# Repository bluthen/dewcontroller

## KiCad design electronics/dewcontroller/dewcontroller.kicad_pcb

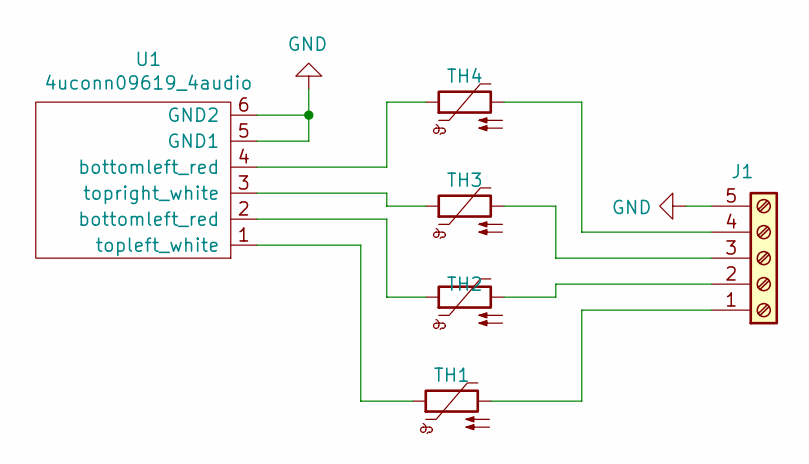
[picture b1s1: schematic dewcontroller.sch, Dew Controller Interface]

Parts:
J1: Screw_Terminal_01x05; 1X05_LOCK_LONGPADS
TH1, TH2, TH3, TH4: Thermistor_PTC; R_Axial_DIN0204_L3.6mm_D1.6mm_P5.08mm_Horizontal
U1: 4uconn09619_4audio; 4ucon09619_4audio

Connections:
GND: J1.5, U1.5 (GND1), U1.6 (GND2)
unnamed: J1.1, TH1.2
unnamed: J1.2, TH2.2
unnamed: J1.3, TH3.2
unnamed: J1.4, TH4.2
unnamed: TH1.1, U1.1 (topleft_white)
unnamed: TH2.1, U1.2 (bottomleft_red)
unnamed: TH3.1, U1.3 (topright_white)
unnamed: TH4.1, U1.4 (bottomleft_red)

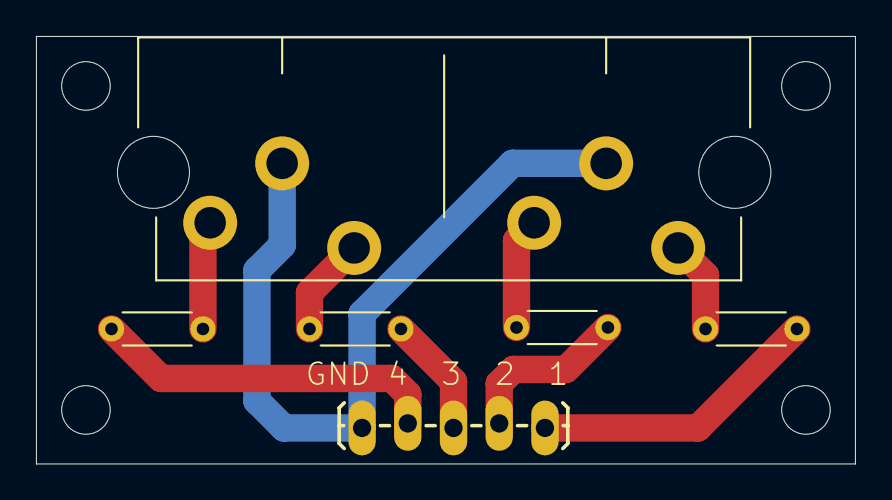
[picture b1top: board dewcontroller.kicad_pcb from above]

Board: 2 copper layers, 45.5 x 23.8 mm, 6 parts (0 on the bottom side), 9 nets.

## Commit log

2022-03-01 Initial commit.
2022-03-07 Fixed wiring on YYNMOS-4 and RCA board.
2022-03-08 Fixed firmware.
2022-03-10 Fixed schematic for using relay board instead of pwm board.
